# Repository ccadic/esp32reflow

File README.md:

# esp32reflow
Small prototype of ESP32 Reflow controller

Today's design: a small ESP32 based reflow controller. PCB made with KICAD. Enclosure made with solidworks. The features: ESP32 LOLIN32 LITE. ILI9341 2.8 display with touch option activated. MAX31865 the temperature probing. 4 buttons (3 on the panel, one on the rotary encoder).  a 110v/220v relay is also there to power the heater plate.  I'm sending the PCB to the factory . Once tested, I'll upload everything on github (opensource)

It is still a proto. I'm waiting for the PCB to arrive

Here you have the first KICAD files
YOu also have the solidworks pre-prototyping files
ALl are subject to modification as the project gores on.

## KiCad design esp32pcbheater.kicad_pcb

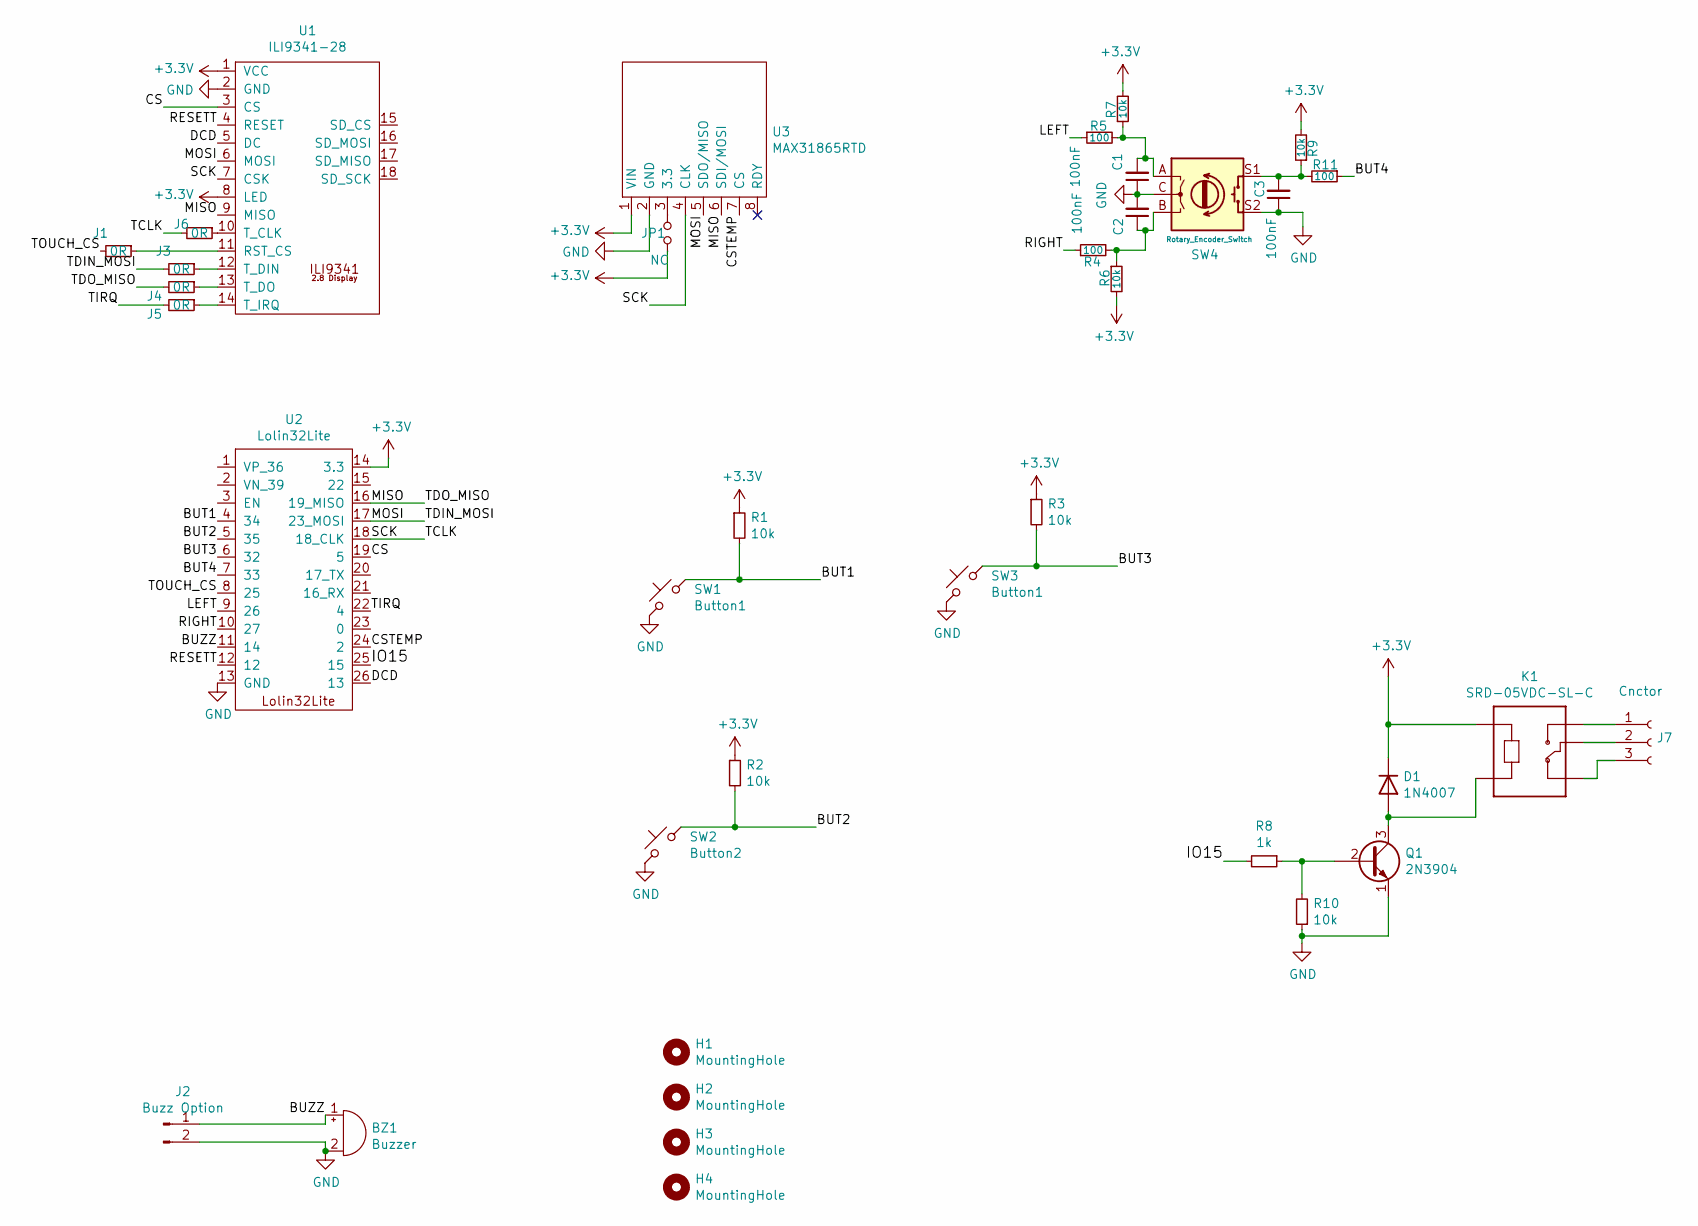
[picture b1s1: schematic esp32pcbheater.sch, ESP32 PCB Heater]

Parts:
BZ1: Buzzer; Buzzer93
C1, C2, C3: 100nF; C_0805_2012Metric
D1: 1N4007; D_DO-41_SOD81_P12.70mm_Horizontal
H1, H2, H3, H4: MountingHole; MountingHole_3mm
J1, J3, J4, J5, J6: 0R; SolderJumper-2_P1.3mm_Open_RoundedPad1.0x1.5mm
J2: Buzz Option; PinHeader_1x02_P2.54mm_Vertical
J7: Cnctor; TerminalBlock_bornier-3_P5.08mm
JP1: NC; JumperSmall
K1: SRD-05VDC-SL-C; RELAY_SRD-05VDC-SL-C
Q1: 2N3904; TO-92L_Inline_Wide
R1, R2, R3, R6, R7, R9, R10: 10k; R_0805_2012Metric
R4, R5, R11: 100; R_0805_2012Metric
R8: 1k; R_0805_2012Metric
SW1, SW3: Button1; SW_TP1003
SW2: Button2; SW_TP1003
SW4: Rotary_Encoder_Switch; RotaryEncoder_Alps_EC11E-Switch_Vertical_H20mm
U1: ILI9341-28; ILI9341-2_8
U2: Lolin32Lite; LOLIN32Lite
U3: MAX31865RTD; MAX31865PCB

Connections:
+3V3: D1.1 (K), JP1.2, K1.1 (A1), R1.1, R2.1, R3.1, R6.2, R7.2, R9.2, U1.1 (VCC), U1.8 (LED), U2.14 (3.3), U3.1 (VIN)
/BUT1: R1.2, SW1.2, U2.4 (34)
/BUT2: R2.2, SW2.2, U2.5 (35)
/BUT3: R3.2, SW3.2, U2.6 (32)
/BUT4: R11.1, U2.7 (33)
/BUZZ: BZ1.1 (-), J2.1, U2.11 (14)
/CS: U1.3 (CS), U2.19 (5)
/CSTEMP: U2.24 (2), U3.7 (CS)
/DCD: U1.5 (DC), U2.26 (13)
/IO15: R8.2, U2.25 (15)
/LEFT: R5.1, U2.9 (26)
/MISO: J4.2, U1.9 (MISO), U2.16 (19_MISO), U3.6 (SDI/MOSI)
/MOSI: J3.2, U1.6 (MOSI), U2.17 (23_MOSI), U3.5 (SDO/MISO)
/RESETT: U1.4 (RESET), U2.12
/RIGHT: R4.1, U2.10 (27)
/SCK: J6.2, U1.7 (CSK), U2.18 (18_CLK), U3.4 (CLK)
/TIRQ: J5.2, U2.22 (4)
/TOUCH_CS: J1.2, U2.8 (25)
GND: BZ1.2 (+), C1.1, C2.2, C3.1, J2.2, Q1.1 (E), R10.1, SW1.1, SW2.1, SW3.1, SW4.C, SW4.S2, U1.2 (GND), U2.13 (GND), U3.2 (GND)
unnamed: C1.2, R5.2, R7.1, SW4.A
unnamed: C2.1, R4.2, R6.1, SW4.B
unnamed: C3.2, R9.1, R11.2, SW4.S1
unnamed: D1.2 (A), K1.4 (A2), Q1.3 (C)
unnamed: J1.1, U1.11 (RST_CS)
unnamed: J3.1, U1.12 (T_DIN)
unnamed: J4.1, U1.13 (T_DO)
unnamed: J5.1, U1.14 (T_IRQ)
unnamed: J6.1, U1.10 (T_CLK)
unnamed: J7.1, K1.3 (NO)
unnamed: J7.2, K1.5 (COM)
unnamed: J7.3, K1.2 (NC)
unnamed: JP1.1, U3.3 (3.3)
unnamed: Q1.2 (B), R8.1, R10.2

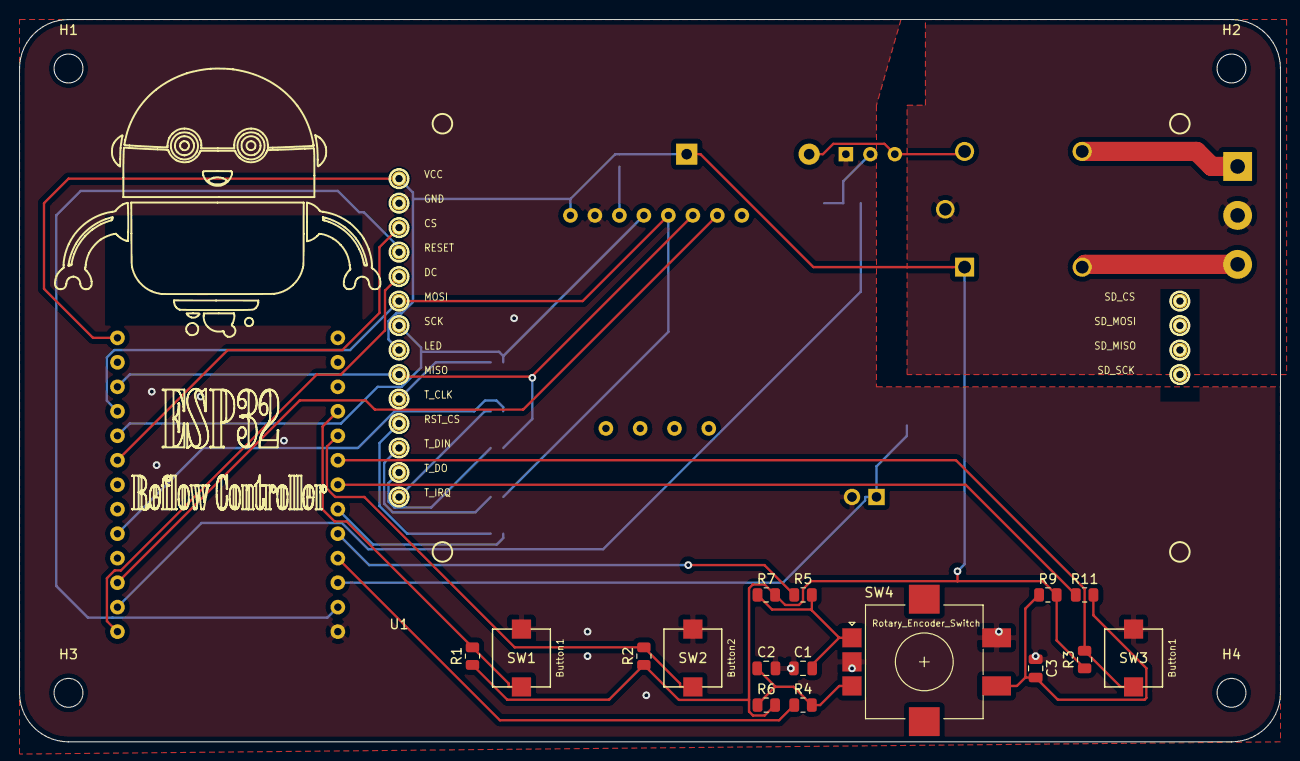
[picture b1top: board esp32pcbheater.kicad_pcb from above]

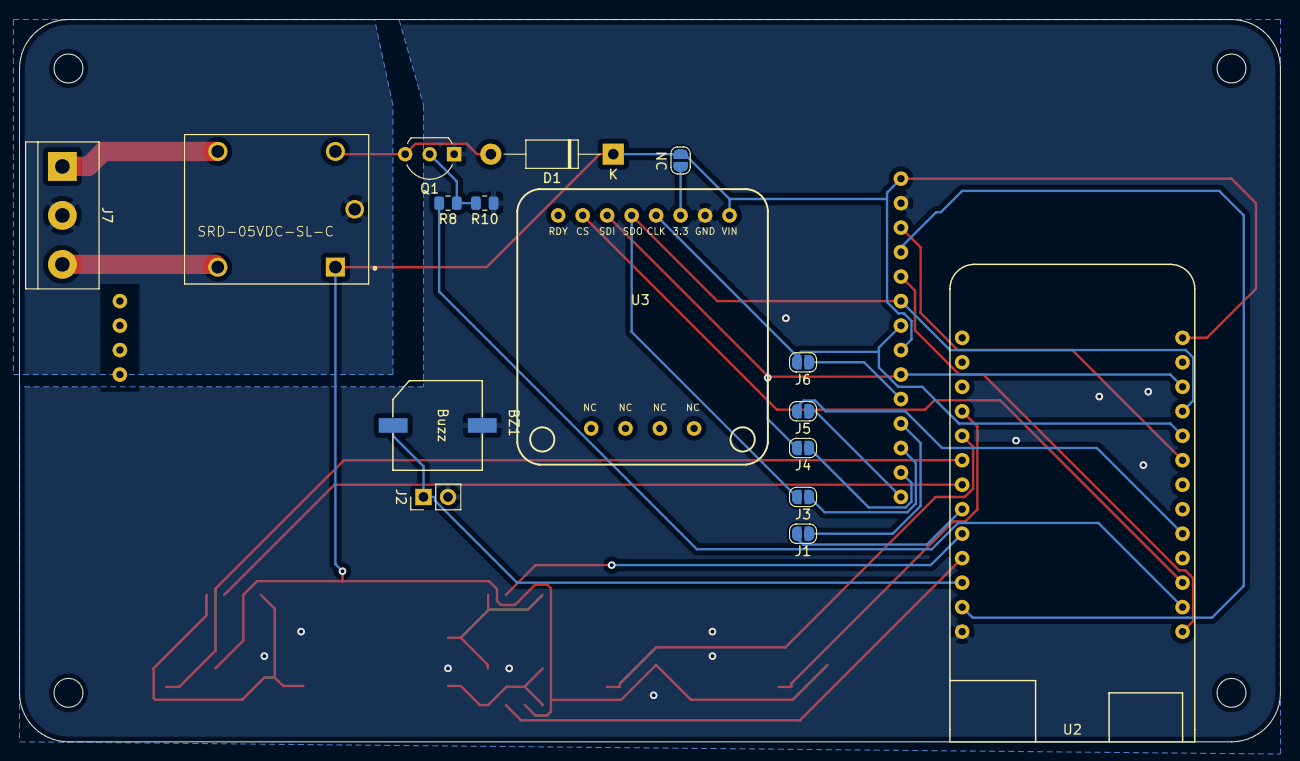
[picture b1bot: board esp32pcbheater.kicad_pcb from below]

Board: 2 copper layers, 130.8 x 74.9 mm, 37 parts (16 on the bottom side), 33 nets.
